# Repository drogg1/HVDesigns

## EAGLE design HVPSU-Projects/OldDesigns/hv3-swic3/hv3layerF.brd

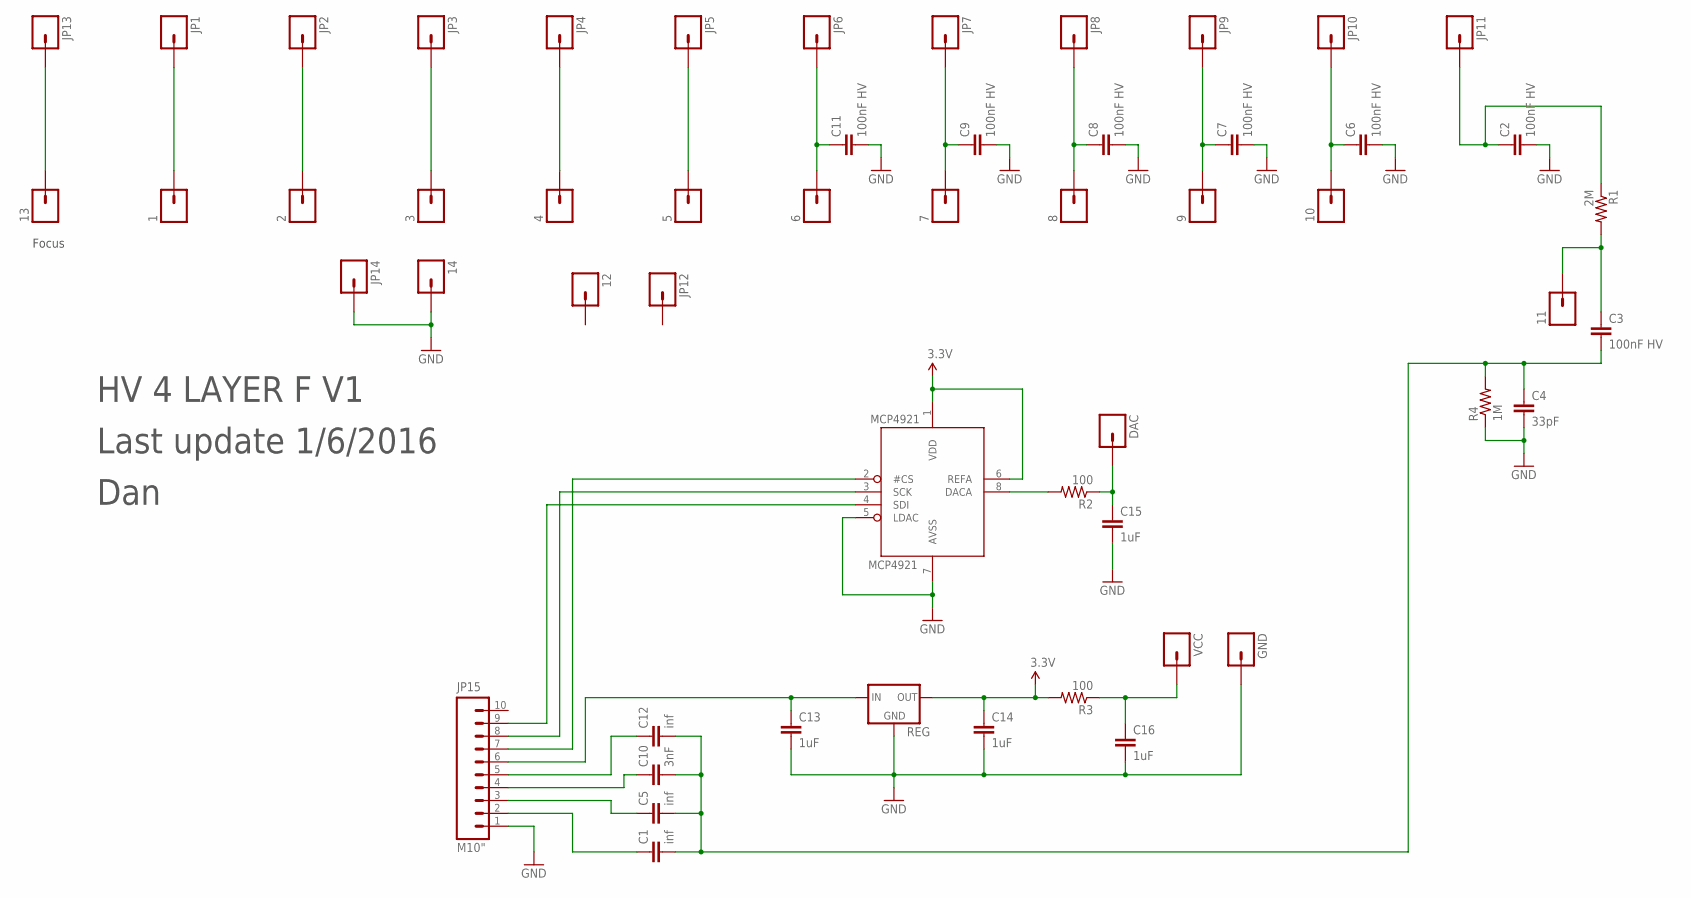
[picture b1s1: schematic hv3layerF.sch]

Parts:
1, 2, 3, 4, 5, 6, 7, 8, 9, 10, 11, 12, 13, 14: M01PTH; 1X01
C1, C5, C12: inf; 0805
C2, C3, C6, C7, C8, C9, C11: 100nF HV; C2225K
C4: 33pF; 0805
C10: 3nF; 0805
C13, C14, C15, C16: 1uF; 0805
DAC: M01PTH; 1X01
GND: M01PTH; 1X01
JP1, JP2, JP3, JP4, JP5, JP6, JP7, JP8, JP9, JP10, JP11, JP12, JP13, JP14: M01PTH; 1X01
JP15: M10"; 1X10
MCP4921: MCP4921D; SO08
R1: 2M; 0805
R2, R3: 100; 0805
R4: 1M; 0805
REG: XC63FPM; SOT23
VCC: M01PTH; 1X01

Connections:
3.3V: C14.1, MCP4921.1 (VDD), MCP4921.6 (REFA), R3.2, REG.2 (OUT)
GND: 14.1, C2.2, C4.2, C6.2, C7.2, C8.2, C9.2, C11.2, C13.2, C14.2, C15.2, C16.2, GND.1, JP14.1, JP15.1, MCP4921.5 (LDAC), MCP4921.7 (AVSS), R4.1, REG.1 (GND)
unnamed: 11.1, C3.1, R1.2
unnamed: C1.1, JP15.2
unnamed: 8.1, C8.1, JP8.1
unnamed: 13.1, JP13.1
unnamed: 9.1, C7.1, JP9.1
unnamed: C5.1, JP15.3
unnamed: 10.1, C6.1, JP10.1
unnamed: C2.1, JP11.1, R1.1
unnamed: C10.1, JP15.4
unnamed: C12.1, JP15.5
unnamed: C13.1, JP15.6, REG.3 (IN)
unnamed: MCP4921.8 (DACA), R2.2
unnamed: C15.1, DAC.1, R2.1
unnamed: C16.1, R3.1, VCC.1
unnamed: 7.1, C9.1, JP7.1
unnamed: JP15.7, MCP4921.2 (#CS)
unnamed: JP15.8, MCP4921.3 (SCK)
unnamed: 6.1, C11.1, JP6.1
unnamed: 5.1, JP5.1
unnamed: JP15.9, MCP4921.4 (SDI)
unnamed: 4.1, JP4.1
unnamed: 3.1, JP3.1
unnamed: 2.1, JP2.1
unnamed: 1.1, JP1.1
PIN3: C1.2, C3.2, C4.1, C5.2, C10.2, C12.2, R4.2

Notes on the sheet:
Focus
HV 4 LAYER F V1
Last update 1/6/2016
Dan

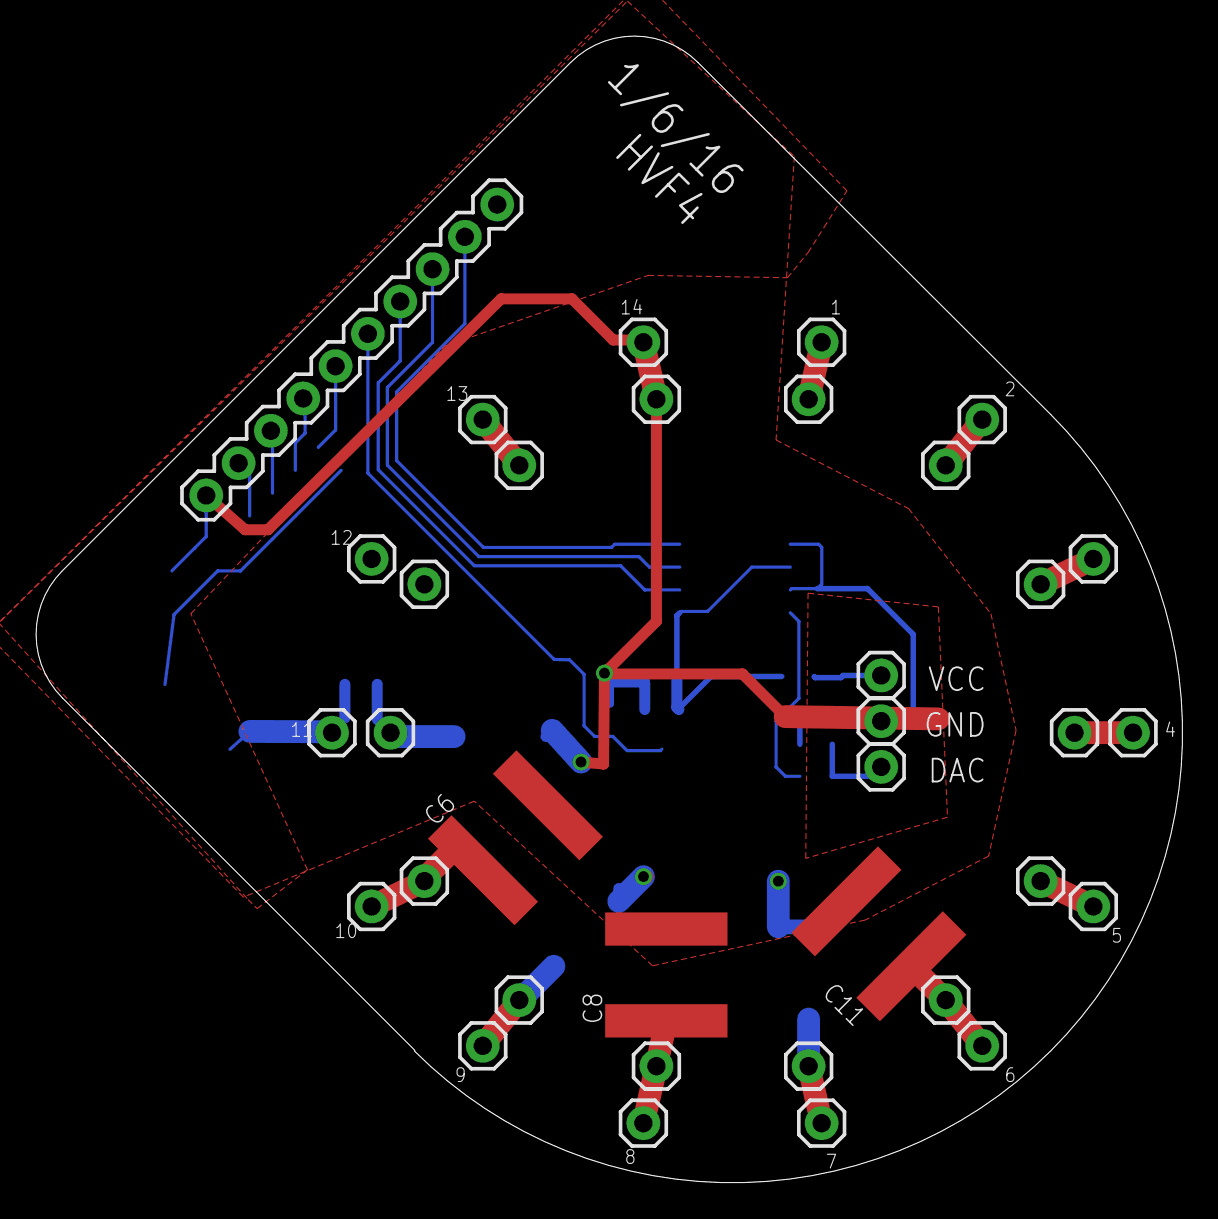
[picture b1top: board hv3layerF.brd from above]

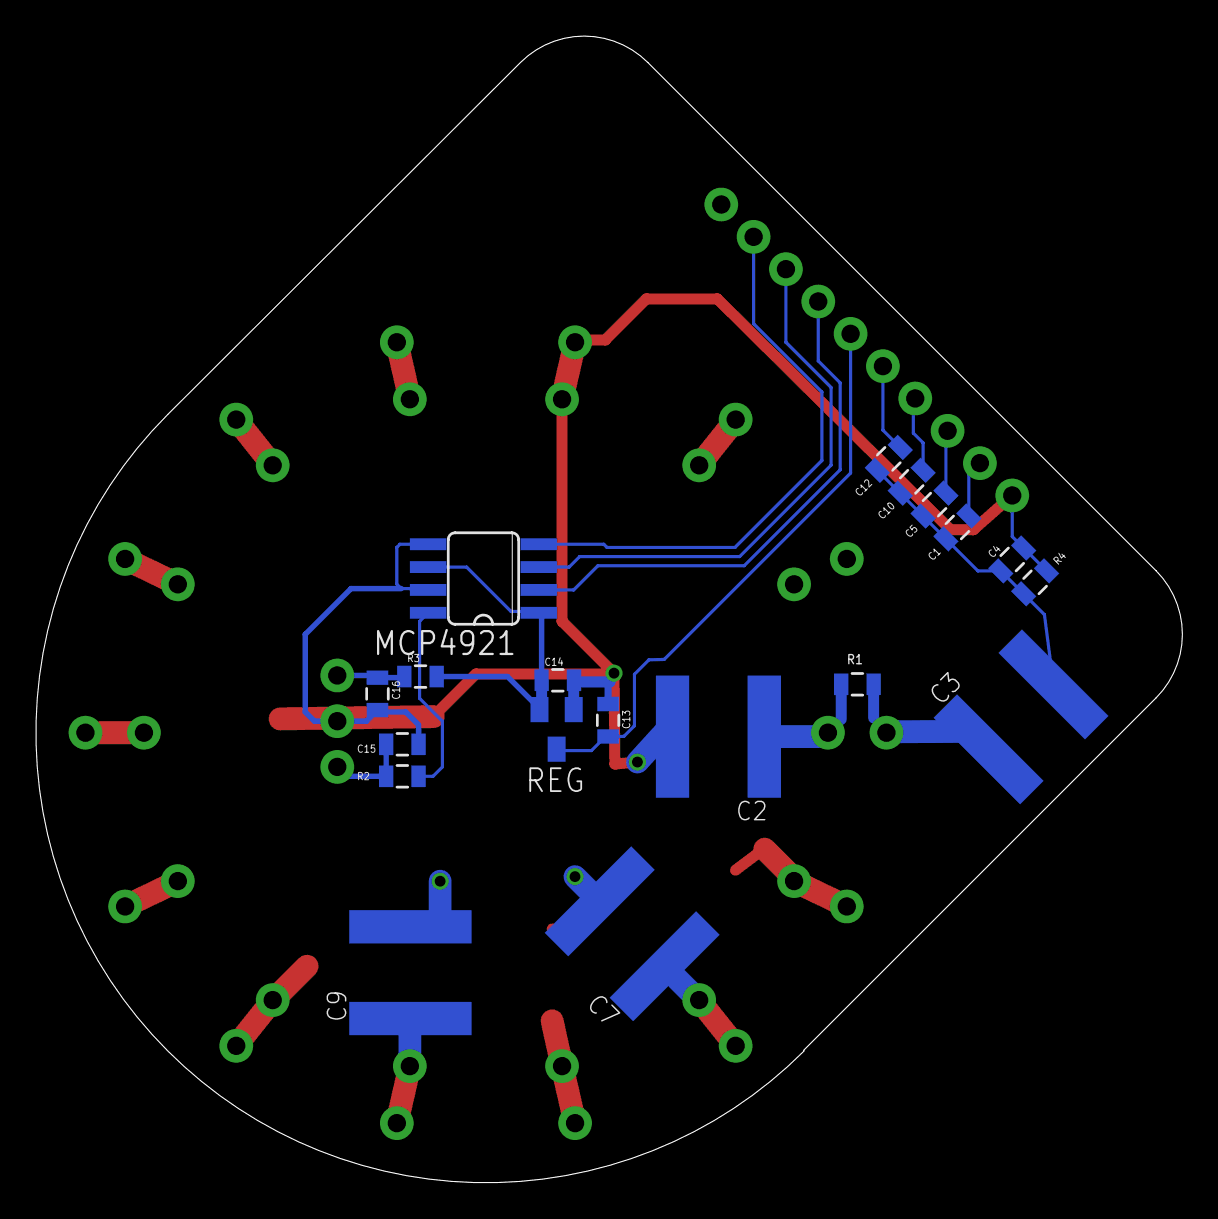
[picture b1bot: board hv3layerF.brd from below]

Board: 2 copper layers, 63.7 x 63.7 mm, 54 parts (19 on the bottom side), 27 nets.

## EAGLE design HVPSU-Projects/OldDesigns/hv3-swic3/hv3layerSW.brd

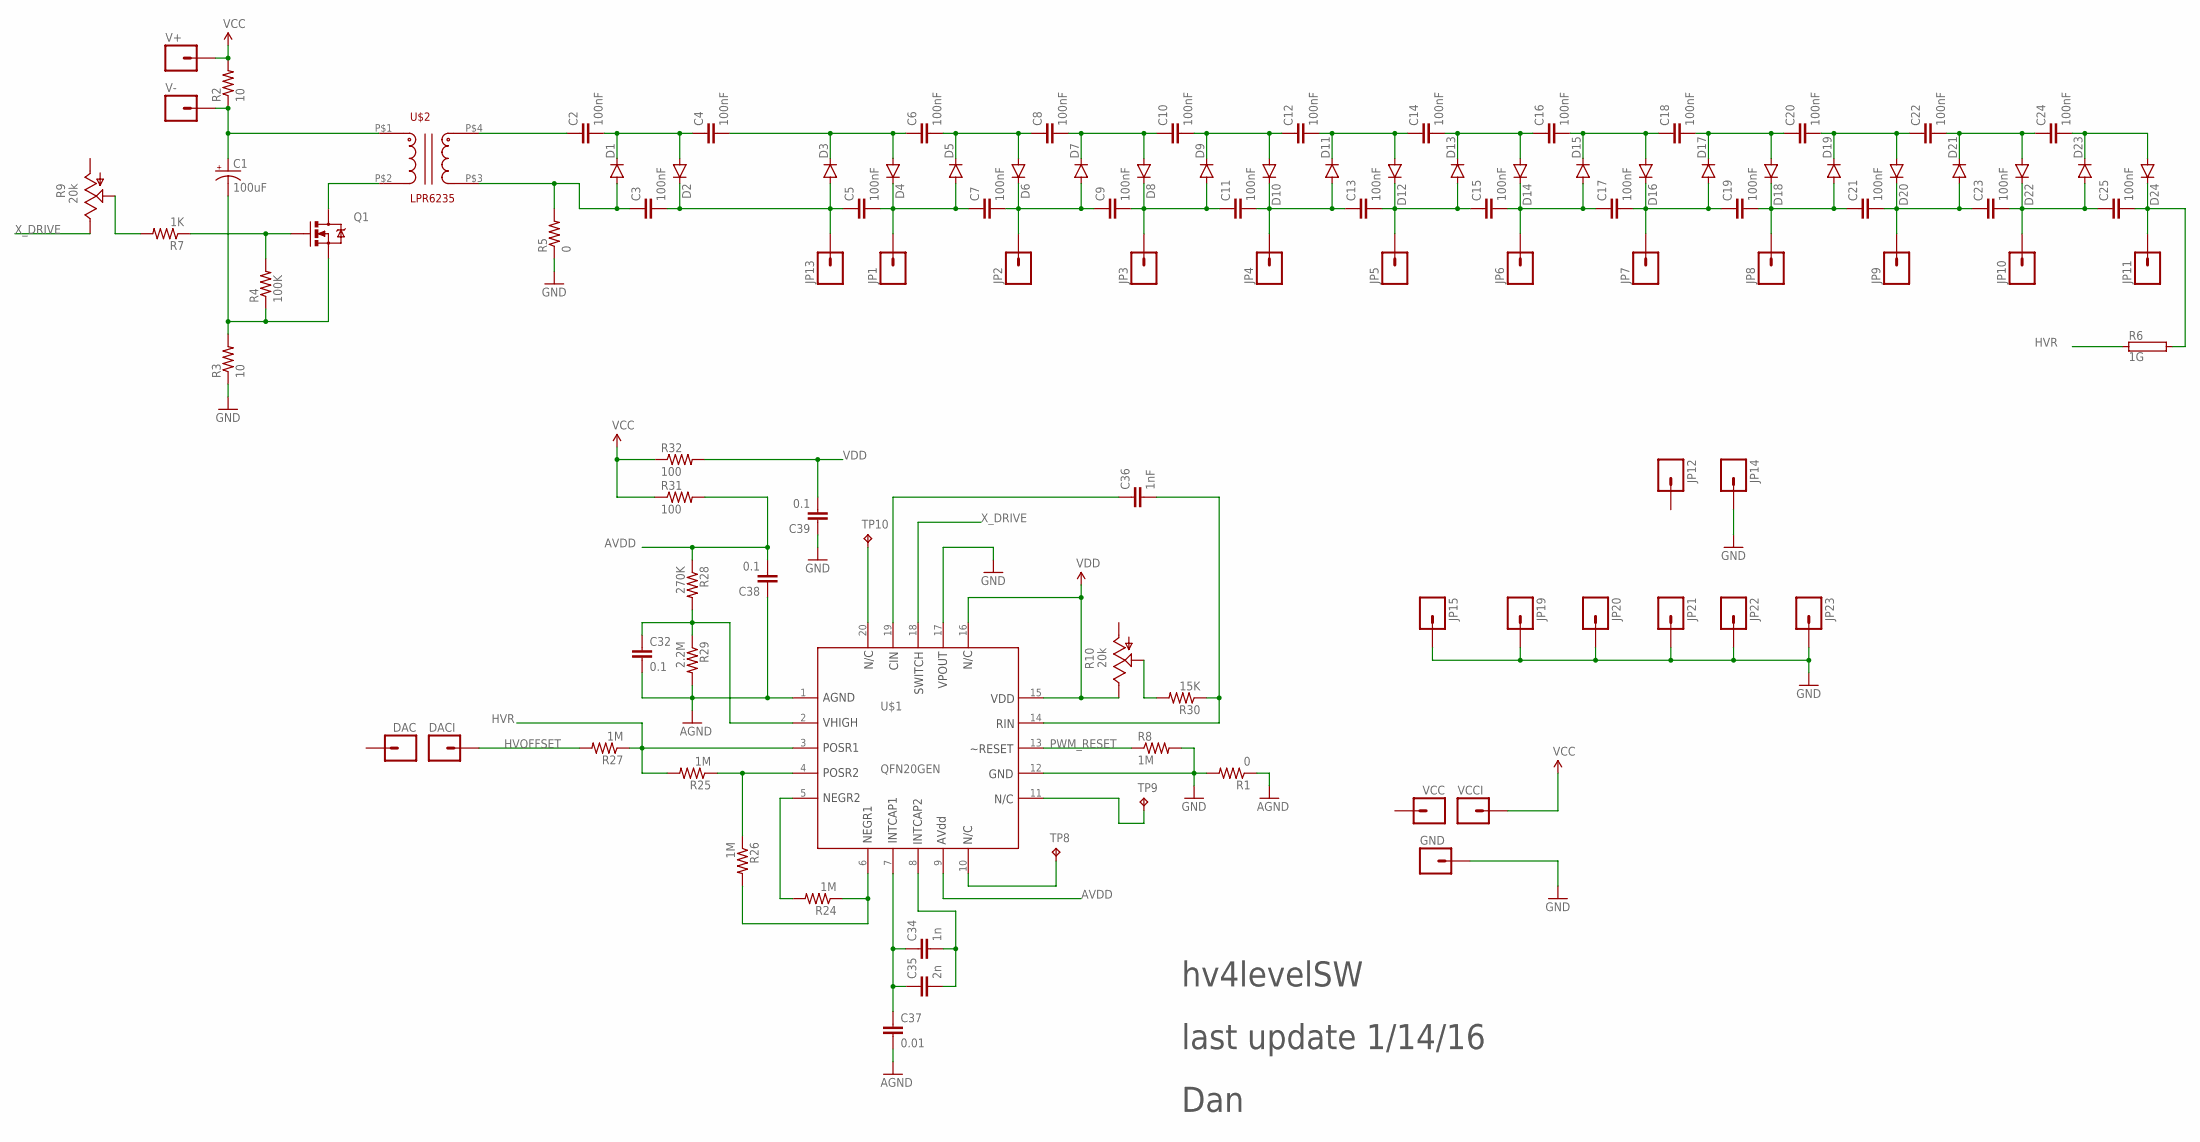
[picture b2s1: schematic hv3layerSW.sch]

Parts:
C1: 100uF; EIA6032
C2, C3, C4, C5, C6, C7, C8, C9, C10, C11, C12, C13, C14, C15, C16, C17, C18, C19, C20, C21, C22, C23, C24, C25: 100nF; 1210
C32, C38, C39: 0.1; 0805
C34: 1n; 0805
C35: 2n; 0805
C36: 1nF; 0805
C37: 0.01; 0805
D1, D2, D3, D4, D5, D6, D7, D8, D9, D10, D11, D12, D13, D14, D15, D16, D17, D18, D19, D20, D21, D22, D23, D24: DIODESOT23; SOT23-3
DAC: M01PTH; 1X01
DACI: M01PTH; 1X01
GND: M01PTH; 1X01
JP1, JP2, JP3, JP4, JP5, JP6, JP7, JP8, JP9, JP10, JP11, JP12, JP13, JP14, JP15, JP19, JP20, JP21, JP22, JP23: M01PTH; 1X01
Q1: MOSFET-NCHANNELAO3404A; SOT23-3
R1, R5: 0; 0805
R2, R3: 10; R2512
R4: 100K; 0805
R6: 1G; CA4090
R7: 1K; 0805
R8, R24, R25, R26, R27: 1M; 0805
R9, R10: 20k; 3223J
R28: 270K; 0805
R29: 2.2M; 0805
R30: 15K; 0805
R31, R32: 100; 0805
TP8, TP9, TP10: TPTP10R; TP10R
U$1: QFN20GEN; QFN20
U$2: LPR6235
V+: M01PTH; 1X01
V-: M01PTH; 1X01
VCC: M01PTH; 1X01
VCCI: M01PTH; 1X01

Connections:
AGND: C32.2, C37.2, C38.1, R1.1, R29.2, U$1.1
AVDD: C38.2, R28.1, R31.2, U$1.9
GND: C39.1, GND.1, JP14.1, JP15.1, JP19.1, JP20.1, JP21.1, JP22.1, JP23.1, R1.2, R3.1, R5.1, R8.2, U$1.12, U$1.17
HVOFFSET: DACI.1, R27.2
HVR: R6.1, R25.2, R27.1, U$1.3
unnamed: C2.1, U$2.P$4 (4)
unnamed: C1.P$2 (-), Q1.2 (S), R3.2, R4.1
unnamed: C3.1, D1.1 (A), R5.2, U$2.P$3 (5)
unnamed: Q1.1 (G), R4.2, R7.1
unnamed: C2.2, C4.1, D1.3 (C), D2.1 (A)
unnamed: R24.1, R26.2, U$1.6
unnamed: Q1.3 (D), U$2.P$2 (2)
unnamed: R10.2 (S), R30.2
unnamed: C3.2, C5.1, D2.3 (C), D3.1 (A), JP13.1
unnamed: C4.2, C6.1, D3.3 (C), D4.1 (A)
unnamed: C5.2, C7.1, D4.3 (C), D5.1 (A), JP1.1
unnamed: C6.2, C8.1, D5.3 (C), D6.1 (A)
unnamed: C7.2, C9.1, D6.3 (C), D7.1 (A), JP2.1
unnamed: C23.2, C25.1, D22.3 (C), D23.1 (A), JP10.1
unnamed: R24.2, U$1.5
unnamed: TP10.TP, U$1.20
unnamed: TP9.TP, U$1.11
unnamed: C8.2, C10.1, D7.3 (C), D8.1 (A)
unnamed: TP8.TP, U$1.10
unnamed: C9.2, C11.1, D8.3 (C), D9.1 (A), JP3.1
unnamed: C1.P$1 (+), R2.1, U$2.P$1 (1), V-.1
unnamed: C10.2, C12.1, D9.3 (C), D10.1 (A)
unnamed: C11.2, C13.1, D10.3 (C), D11.1 (A), JP4.1
unnamed: C12.2, C14.1, D11.3 (C), D12.1 (A)
unnamed: C14.2, C16.1, D13.3 (C), D14.1 (A)
unnamed: C13.2, C15.1, D12.3 (C), D13.1 (A), JP5.1
unnamed: C15.2, C17.1, D14.3 (C), D15.1 (A), JP6.1
unnamed: C17.2, C19.1, D16.3 (C), D17.1 (A), JP7.1
unnamed: C19.2, C21.1, D18.3 (C), D19.1 (A), JP8.1
unnamed: C16.2, C18.1, D15.3 (C), D16.1 (A)
unnamed: C18.2, C20.1, D17.3 (C), D18.1 (A)
unnamed: C20.2, C22.1, D19.3 (C), D20.1 (A)
unnamed: C21.2, C23.1, D20.3 (C), D21.1 (A), JP9.1
unnamed: C22.2, C24.1, D21.3 (C), D22.1 (A)
unnamed: C24.2, D23.3 (C), D24.1 (A)
unnamed: C25.2, D24.3 (C), JP11.1, R6.2
unnamed: R7.2, R9.2 (S)
unnamed: C34.1, C35.1, C37.1, U$1.7
unnamed: R25.1, R26.1, U$1.4
unnamed: C34.2, C35.2, U$1.8
unnamed: C32.1, R28.2, R29.1, U$1.2
unnamed: C36.2, R30.1, U$1.14
unnamed: C36.1, U$1.19
PWM_RESET: R8.1, U$1.13
VCC: R2.2, R31.1, R32.1, V+.1, VCCI.1
VDD: C39.2, R10.3 (E), R32.2, U$1.15, U$1.16
X_DRIVE: R9.3 (E), U$1.18

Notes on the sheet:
last update 1/14/16
Dan
hv4levelSW

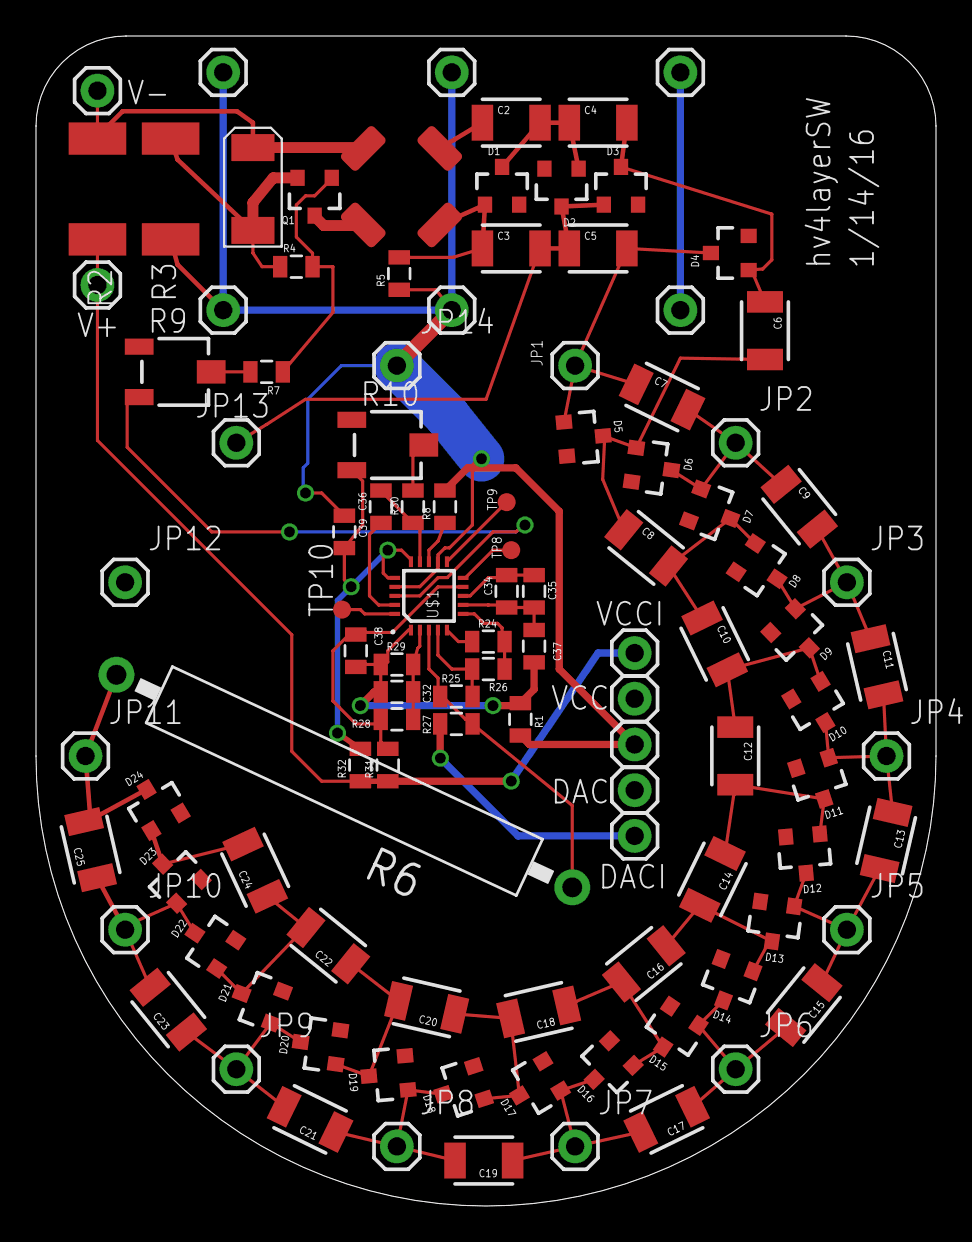
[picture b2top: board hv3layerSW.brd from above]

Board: 2 copper layers, 50.0 x 65.0 mm, 108 parts (0 on the bottom side), 52 nets.

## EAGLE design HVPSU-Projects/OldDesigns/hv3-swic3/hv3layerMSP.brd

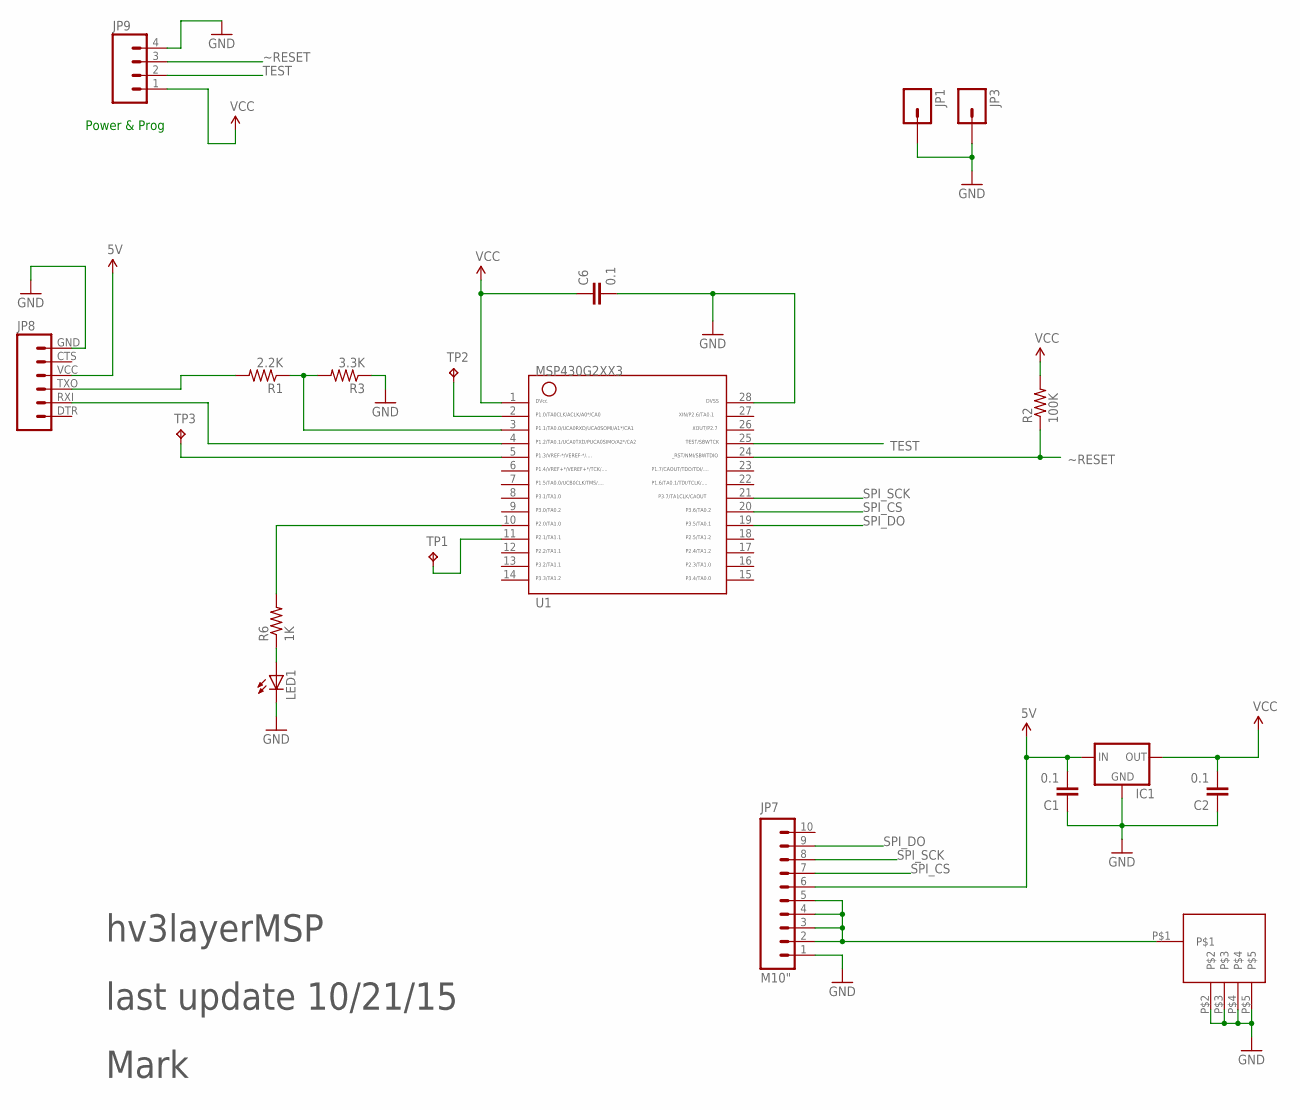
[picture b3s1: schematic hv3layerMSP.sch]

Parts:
C1, C2, C6: 0.1; 0805
IC1: XC63FPM; SOT23
JP1, JP3: M01PTH; 1X01
JP7: M10"; 1X10
JP8: M06SIP; 1X06
JP9: M04PTH; 1X04
LED1: LEDSML0805; SML0805
R1: 2.2K; 0805
R2: 100K; 0805
R3: 3.3K; 0805
R6: 1K; 0805
TP1, TP2, TP3: TPTP10R; TP10R
U1: G2XX3---PW28; PW28
U$2: SMA; SMA_EDGE

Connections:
5V: C1.2, IC1.3 (IN), JP7.6, JP8.VCC (4)
GND: C1.1, C2.1, C6.2, IC1.1 (GND), JP1.1, JP3.1, JP7.1, JP8.GND (6), JP9.4, LED1.C, R3.1, U1.28, U$2.P$2, U$2.P$3, U$2.P$4, U$2.P$5
unnamed: TP1.TP, U1.11
unnamed: TP2.TP, U1.2
unnamed: TP3.TP, U1.5
unnamed: R6.2, U1.10
unnamed: JP8.TXO (3), R1.2
unnamed: R1.1, R3.2, U1.3
unnamed: JP8.RXI (2), U1.4
unnamed: LED1.A, R6.1
unnamed: JP7.2, JP7.3, JP7.4, JP7.5, U$2.P$1
SPI_CS: JP7.7, U1.20
SPI_DO: JP7.9, U1.19
SPI_SCK: JP7.8, U1.21
TEST: JP9.2, U1.25
VCC: C2.2, C6.1, IC1.2 (OUT), JP9.1, R2.2, U1.1
~RESET: JP9.3, R2.1, U1.24

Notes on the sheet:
Power & Prog
last update 10/21/15
Mark
hv3layerMSP

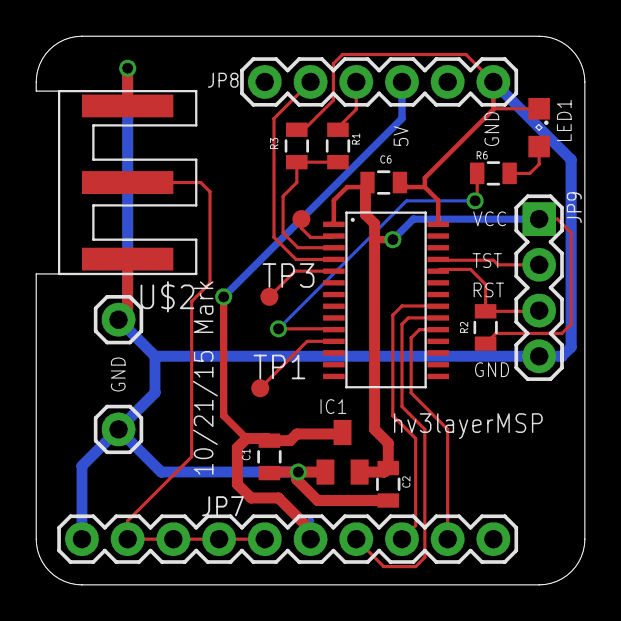
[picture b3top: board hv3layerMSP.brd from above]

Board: 2 copper layers, 30.5 x 30.5 mm, 19 parts (0 on the bottom side), 17 nets.

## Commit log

2019-03-03 latest
2019-03-03 Added CCS test code for HV supplies.
2019-03-04 Working on the test code. Shifting data into the DAC I believe works. Need to test the I2C code needed to communicate with the HV Measurement ADC.
2019-03-25 Latest code. Should work to test supplies and output HV anode voltage.

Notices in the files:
parts and their libraries:
SparkFun-Capacitors: Licensing: CC v3.0 Share-Alike You are welcome to use this library for commercial purposes.
SparkFun-Connectors: Licensing: Creative Commons ShareAlike 4.0 International - https://creativecommons.org/licenses/by-sa/4.0
